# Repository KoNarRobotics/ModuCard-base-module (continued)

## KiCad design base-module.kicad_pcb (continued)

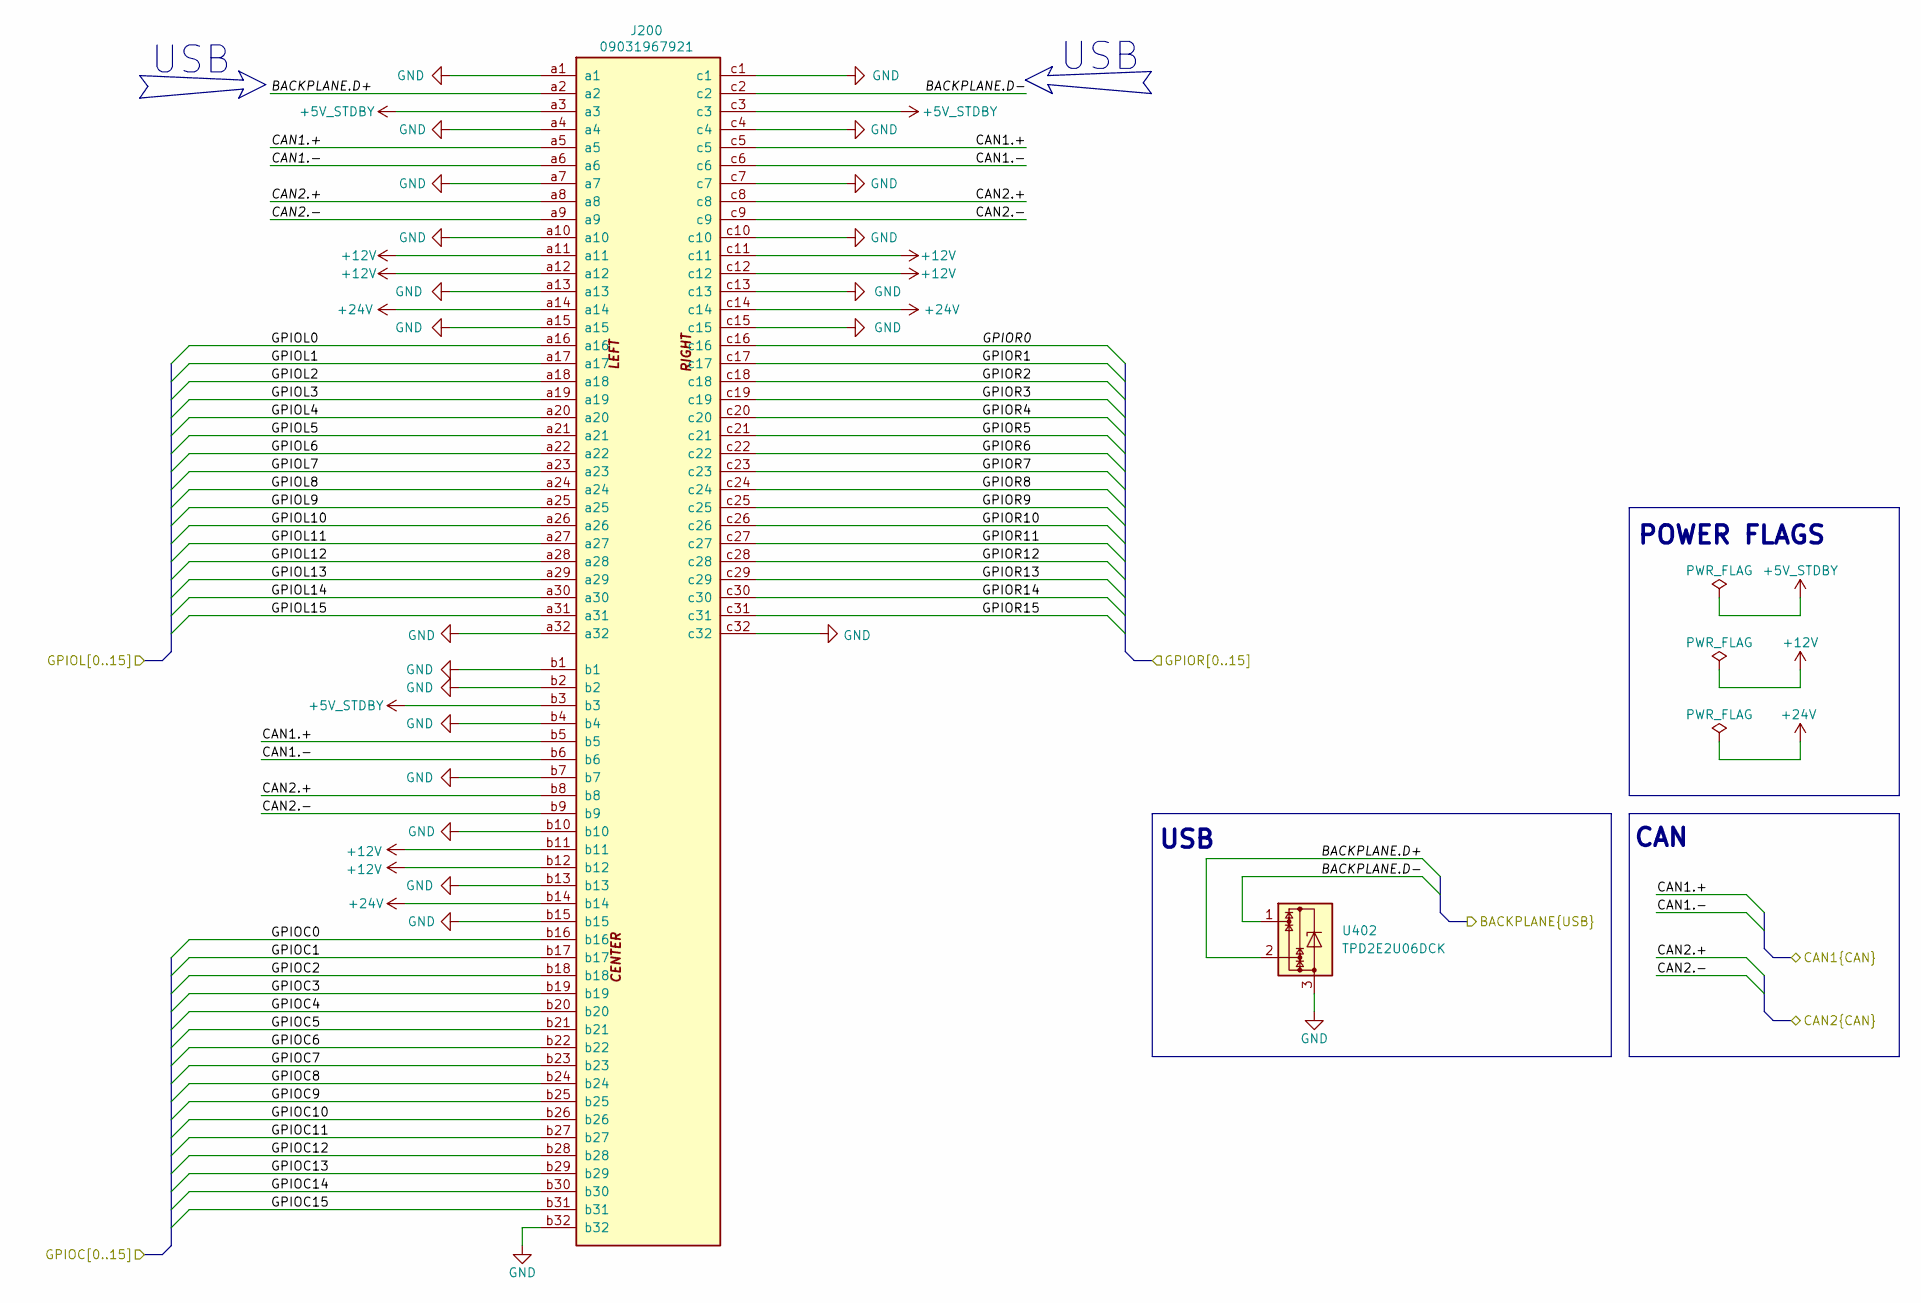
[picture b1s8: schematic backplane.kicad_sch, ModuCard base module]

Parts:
J200: 09031967921; DIN41612_R_3x32_Female_Horizontal_THT; PARTREV D
U402: TPD2E2U06DCK; SOT-323_SC-70

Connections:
+5V_STDBY: J200.a3, J200.b3, J200.c3
+12V: J200.a11, J200.a12, J200.b11, J200.b12, J200.c11, J200.c12; also elsewhere on the board
+24V: J200.a14, J200.b14, J200.c14
/Backplane/BACKPLANE.D+: J200.a2, U402.2; also elsewhere on the board
/Backplane/BACKPLANE.D-: J200.c2, U402.1; also elsewhere on the board
/Backplane/CAN1.+: J200.a5, J200.b5, J200.c5; also elsewhere on the board
/Backplane/CAN1.-: J200.a6, J200.b6, J200.c6; also elsewhere on the board
/Backplane/CAN2.+: J200.a8, J200.b8, J200.c8; also elsewhere on the board
/Backplane/CAN2.-: J200.a9, J200.b9, J200.c9; also elsewhere on the board
/Backplane/GPIOC0: J200.b16
/Backplane/GPIOC1: J200.b17
/Backplane/GPIOC2: J200.b18
/Backplane/GPIOC3: J200.b19
/Backplane/GPIOC4: J200.b20
/Backplane/GPIOC5: J200.b21
/Backplane/GPIOC6: J200.b22
/Backplane/GPIOC7: J200.b23
/Backplane/GPIOC8: J200.b24
/Backplane/GPIOC9: J200.b25
/Backplane/GPIOC10: J200.b26
/Backplane/GPIOC11: J200.b27
/Backplane/GPIOC12: J200.b28
/Backplane/GPIOC13: J200.b29
/Backplane/GPIOC14: J200.b30
/Backplane/GPIOC15: J200.b31
/Backplane/GPIOL0: J200.a16
/Backplane/GPIOL1: J200.a17
/Backplane/GPIOL2: J200.a18
/Backplane/GPIOL3: J200.a19
/Backplane/GPIOL4: J200.a20
/Backplane/GPIOL5: J200.a21
/Backplane/GPIOL6: J200.a22
/Backplane/GPIOL7: J200.a23
/Backplane/GPIOL8: J200.a24
/Backplane/GPIOL9: J200.a25
/Backplane/GPIOL10: J200.a26
/Backplane/GPIOL11: J200.a27
/Backplane/GPIOL12: J200.a28
/Backplane/GPIOL13: J200.a29
/Backplane/GPIOL14: J200.a30
/Backplane/GPIOL15: J200.a31
/Backplane/GPIOR0: J200.c16
/Backplane/GPIOR1: J200.c17
/Backplane/GPIOR2: J200.c18
/Backplane/GPIOR3: J200.c19
/Backplane/GPIOR4: J200.c20
/Backplane/GPIOR5: J200.c21
/Backplane/GPIOR6: J200.c22
/Backplane/GPIOR7: J200.c23
/Backplane/GPIOR8: J200.c24
/Backplane/GPIOR9: J200.c25
/Backplane/GPIOR10: J200.c26
/Backplane/GPIOR11: J200.c27
/Backplane/GPIOR12: J200.c28
/Backplane/GPIOR13: J200.c29
/Backplane/GPIOR14: J200.c30
/Backplane/GPIOR15: J200.c31
GND: J200.a1, J200.a4, J200.a7, J200.a10, J200.a13, J200.a15, J200.a32, J200.b1, J200.b2, J200.b4, J200.b7, J200.b10, J200.b13, J200.b15, J200.b32, J200.c1, J200.c4, J200.c7, J200.c10, J200.c13, J200.c15, J200.c32, U402.3; also elsewhere on the board

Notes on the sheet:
USB
CAN
POWER FLAGS
USB

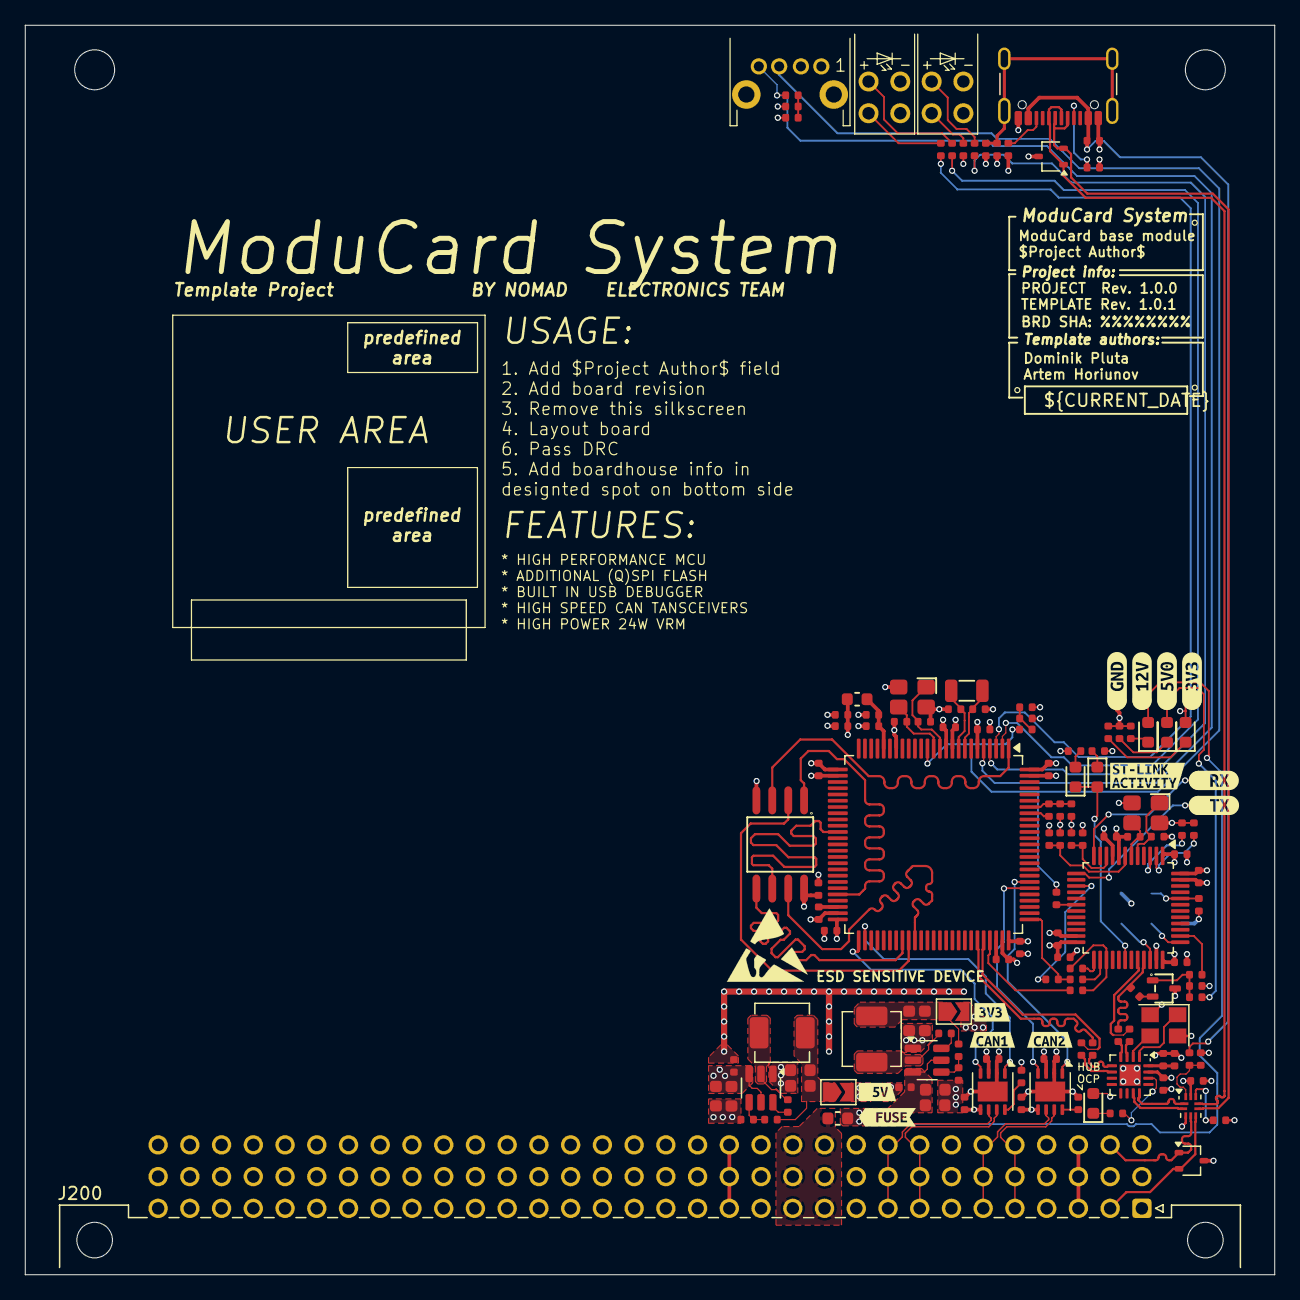
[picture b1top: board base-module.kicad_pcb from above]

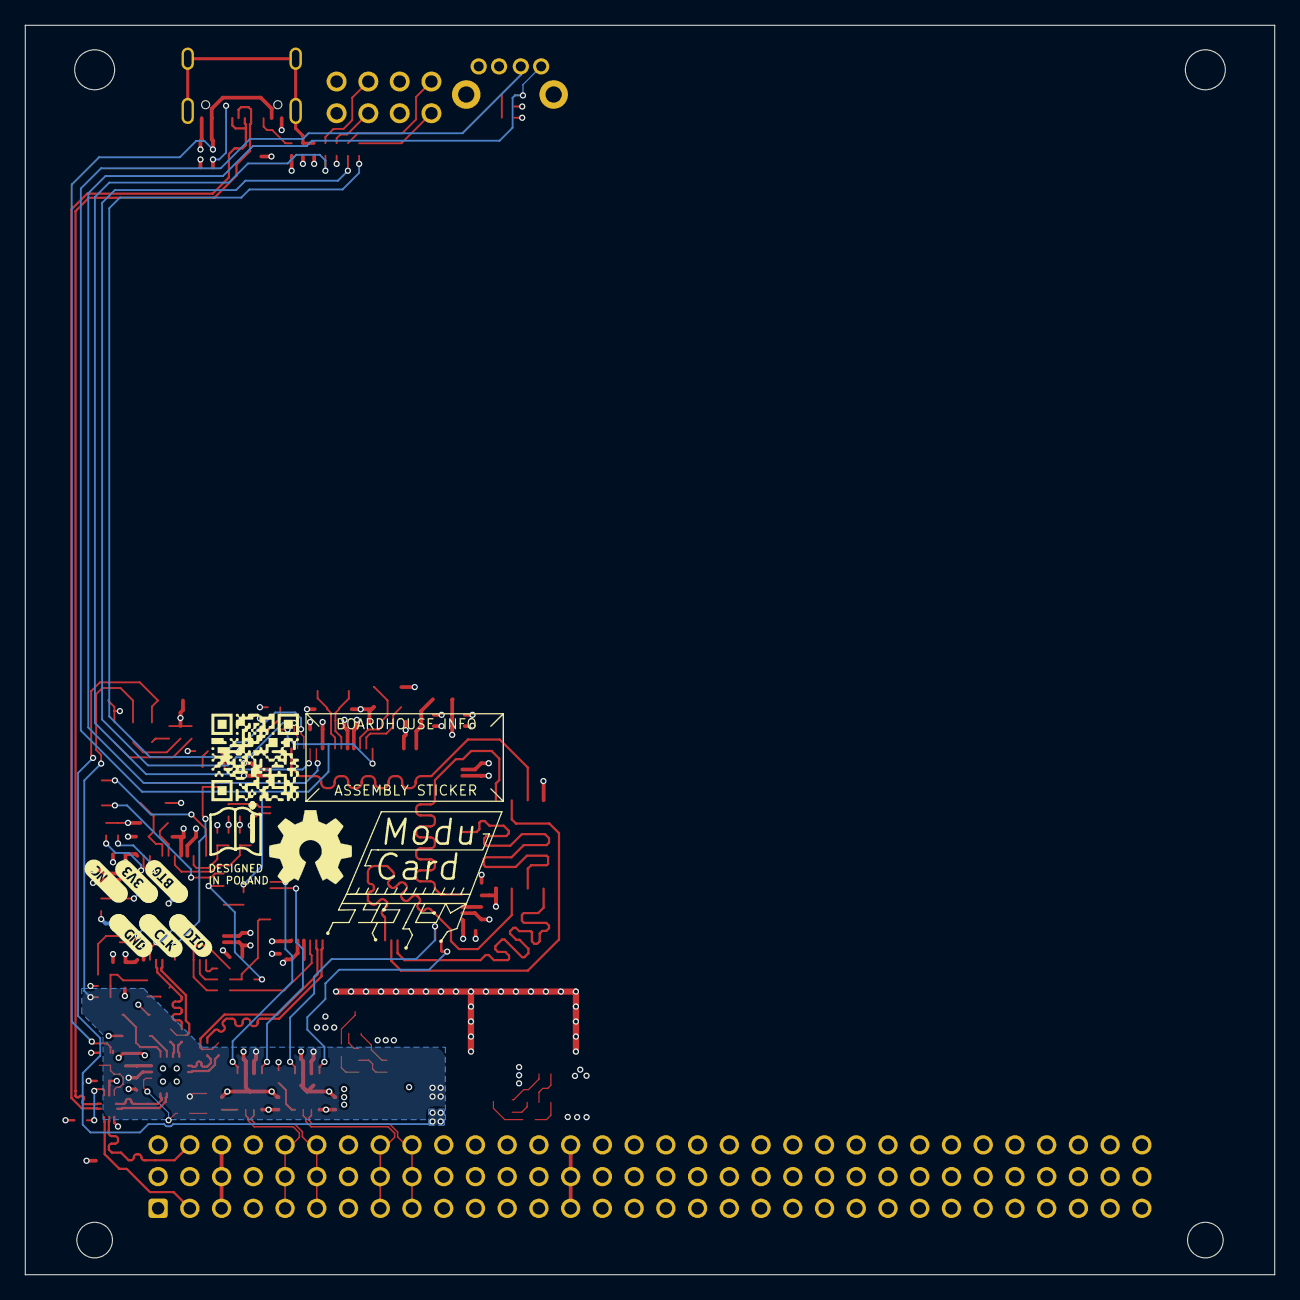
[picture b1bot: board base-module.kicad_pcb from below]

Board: 4 copper layers, 100.0 x 100.0 mm, 160 parts (11 on the bottom side), 103 nets.

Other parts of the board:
kibuzzard-67B20BD5: G***; kibuzzard-67B20BD5
kibuzzard-67B63E8D: G***; kibuzzard-67B63E8D
kibuzzard-67B219C6: G***; kibuzzard-67B219C6
kibuzzard-67B624A4: G***; kibuzzard-67B624A4
kibuzzard-67B643AC: G***; kibuzzard-67B643AC
kibuzzard-67B643DE: G***; kibuzzard-67B643DE
kibuzzard-67B643EE: G***; kibuzzard-67B643EE
kibuzzard-67B2198C: G***; kibuzzard-67B2198C
kibuzzard-67B6248A: G***; kibuzzard-67B6248A
kibuzzard-67B6249A: G***; kibuzzard-67B6249A
kibuzzard-67B6438D: G***; kibuzzard-67B6438D
kibuzzard-67B37005: G***; kibuzzard-67B37005
kibuzzard-67B37418: G***; kibuzzard-67B37418
kibuzzard-67B37472: G***; kibuzzard-67B37472
kibuzzard-67B62451: G***; kibuzzard-67B62451
kibuzzard-67B62470: G***; kibuzzard-67B62470
kibuzzard-67BE3F52: G***; kibuzzard-67BE3F52
kibuzzard-67E7D86B: G***; kibuzzard-67E7D86B

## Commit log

2025-02-08 [2] Update converter layout
2025-02-08 [2] Add JLC4161H stackup
2025-02-08 [2] Setup pre-defined track widths and via sizes, start ST-LINK layout
2025-02-08 [2] Add footprints
2025-02-08 [2] Improve layout
2025-02-08 [2] Change layout
2025-02-08 [2] Group more elements
2025-02-08 [2] Fix component placements
2025-02-13 WIP: [3] Fix USB bus naming on schematic
2025-02-13 [3] Choose components from JLC, fix connections on the shcematic
2025-02-13 [3] Fix buses naming on schematic
2025-02-13 [3] Refactor and annotate schematic
2025-02-13 [3] Clear ERC errors
2025-02-13 [3] Fix CAN bus naming on schematic
2025-02-13 [3] Fix MCU NRST connection
2025-02-13 [2] Add TL2243 Double stack switch library
2025-02-13 [2] Add Upright USB library
2025-02-13 [2] Add TL2243 Description and Datasheet
2025-02-13 [2] Add USB and double button, assign testpoint footprints
2025-02-13 [2] Change USB connector, add board outline and information about keepout area
2025-04-18 Revert "1 change mcu schematic "
2025-04-18 Add generated schematic PDF and Gerber files
